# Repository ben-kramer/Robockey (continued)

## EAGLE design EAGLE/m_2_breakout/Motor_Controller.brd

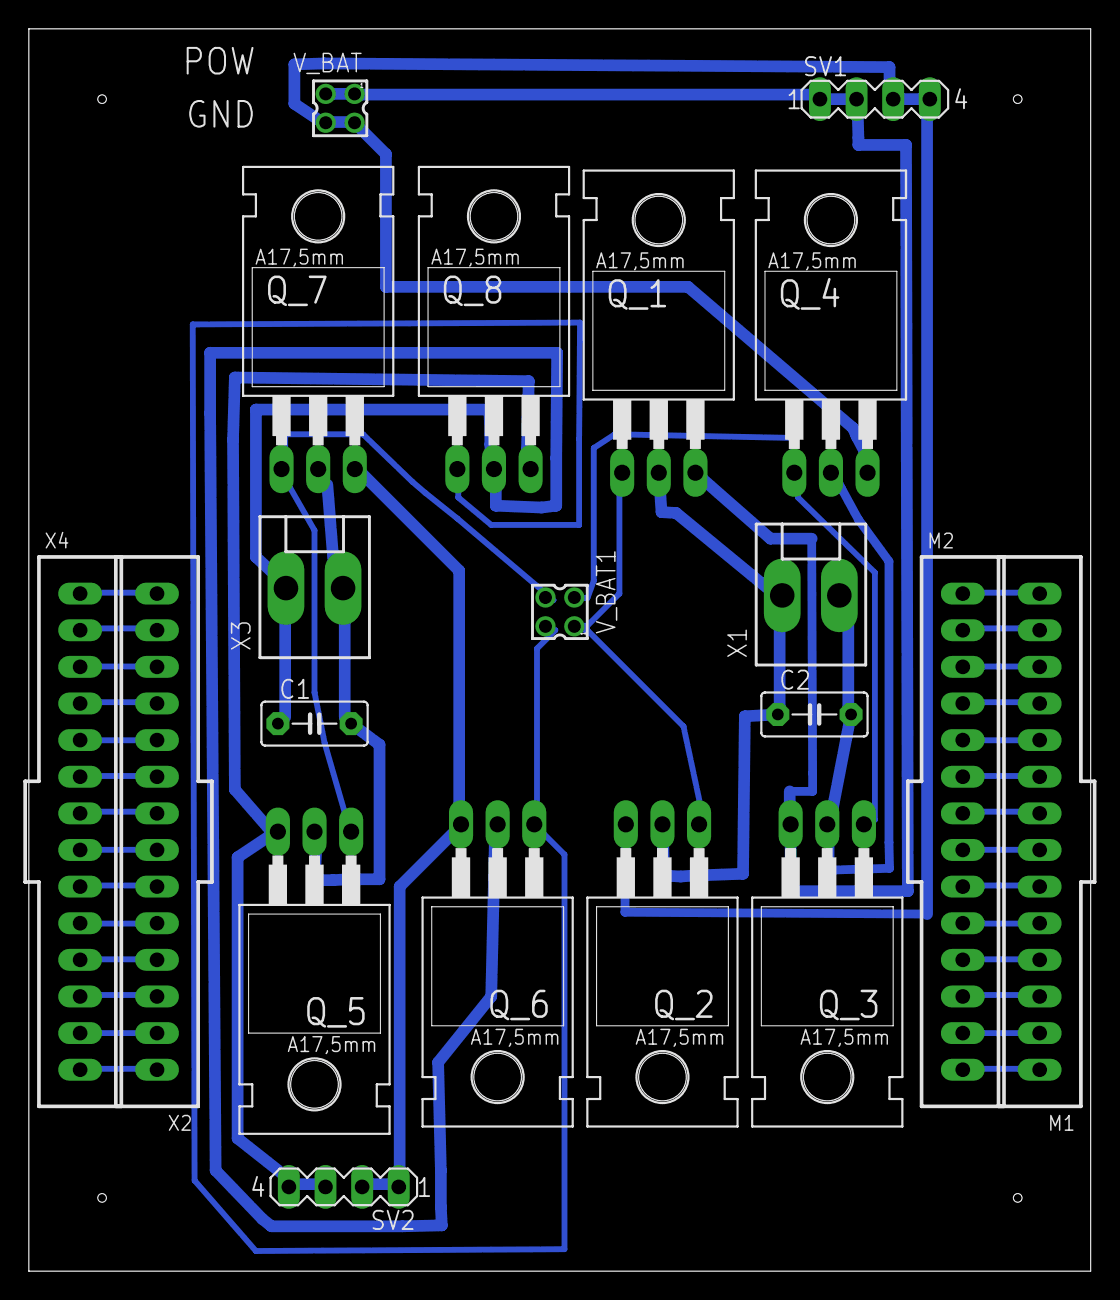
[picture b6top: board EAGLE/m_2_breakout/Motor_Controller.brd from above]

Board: 2 copper layers, 73.6 x 86.2 mm, 20 parts (0 on the bottom side), 40 nets.

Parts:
C1, C2: C5B3
M1, M2: C-GRID-14-70543; 70543-14
Q_1, Q_3, Q_6, Q_7: IRF4905; TO220BH
Q_2, Q_4, Q_5, Q_8: IRFZ48Z; TO220BH
SV1, SV2: MA04-1
V_BAT, V_BAT1: 87758-0416
X1, X3: KK-156-2
X2, X4: C-GRID-14-70543; 70543-14

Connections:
GND1: Q_2.S, Q_4.S, SV1.3, SV1.4, V_BAT.2, V_BAT.4
GND2: Q_5.S, Q_8.S, SV2.3, SV2.4
ML+: C1.1, Q_6.D, Q_8.D, X3.1
ML-: C1.2, Q_5.D, Q_7.D, X3.2
ML_G+: Q_6.G, Q_8.G, V_BAT1.2
ML_G-: Q_5.G, Q_7.G, V_BAT1.4
MR+: C2.1, Q_1.D, Q_2.D, X1.1
MR-: C2.2, Q_3.D, Q_4.D, X1.2
MR_G+: Q_1.G, Q_2.G, V_BAT1.1
MR_G-: Q_3.G, Q_4.G, V_BAT1.3
unnamed: M1.1, M2.14
unnamed: M1.2, M2.13
unnamed: M1.3, M2.12
unnamed: M1.4, M2.11
unnamed: M1.5, M2.10
unnamed: M1.6, M2.9
unnamed: M1.7, M2.8
unnamed: M1.8, M2.7
unnamed: M1.9, M2.6
unnamed: M1.10, M2.5
unnamed: M1.11, M2.4
unnamed: M1.12, M2.3
unnamed: M1.13, M2.2
unnamed: M1.14, M2.1
unnamed: X2.1, X4.14
unnamed: X2.2, X4.13
unnamed: X2.3, X4.12
unnamed: X2.4, X4.11
unnamed: X2.5, X4.10
unnamed: X2.6, X4.9
unnamed: X2.7, X4.8
unnamed: X2.8, X4.7
unnamed: X2.9, X4.6
unnamed: X2.10, X4.5
unnamed: X2.11, X4.4
unnamed: X2.12, X4.3
unnamed: X2.13, X4.2
unnamed: X2.14, X4.1
POW1: Q_1.S, Q_3.S, SV1.1, SV1.2, V_BAT.1, V_BAT.3
POW2: Q_6.S, Q_7.S, SV2.1, SV2.2

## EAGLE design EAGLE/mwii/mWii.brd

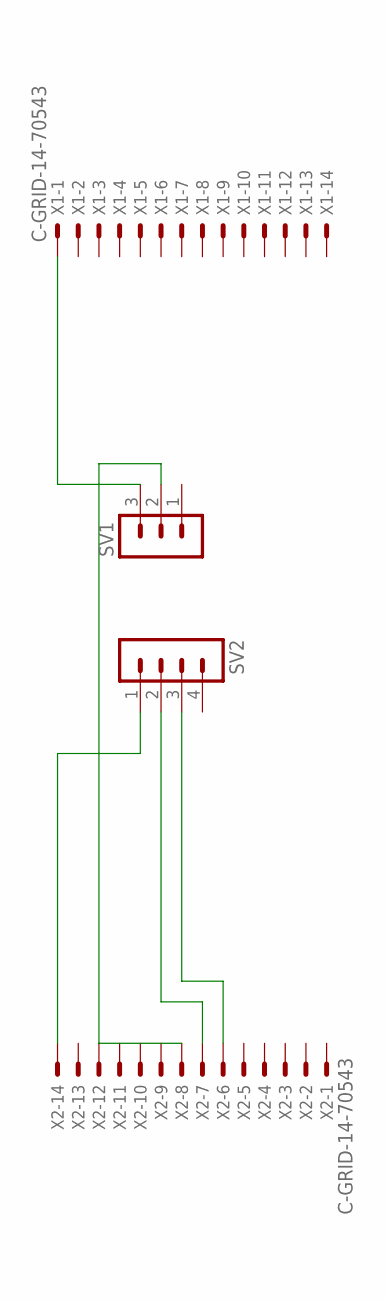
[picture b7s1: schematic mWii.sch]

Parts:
SV1: MA03-1
SV2: MA04-1
X1, X2: C-GRID-14-70543; 70543-14

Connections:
unnamed: SV2.1, X2.14
unnamed: SV1.3, X1.1
unnamed: SV1.2, X2.8
unnamed: SV2.2, X2.7
unnamed: SV2.3, X2.6

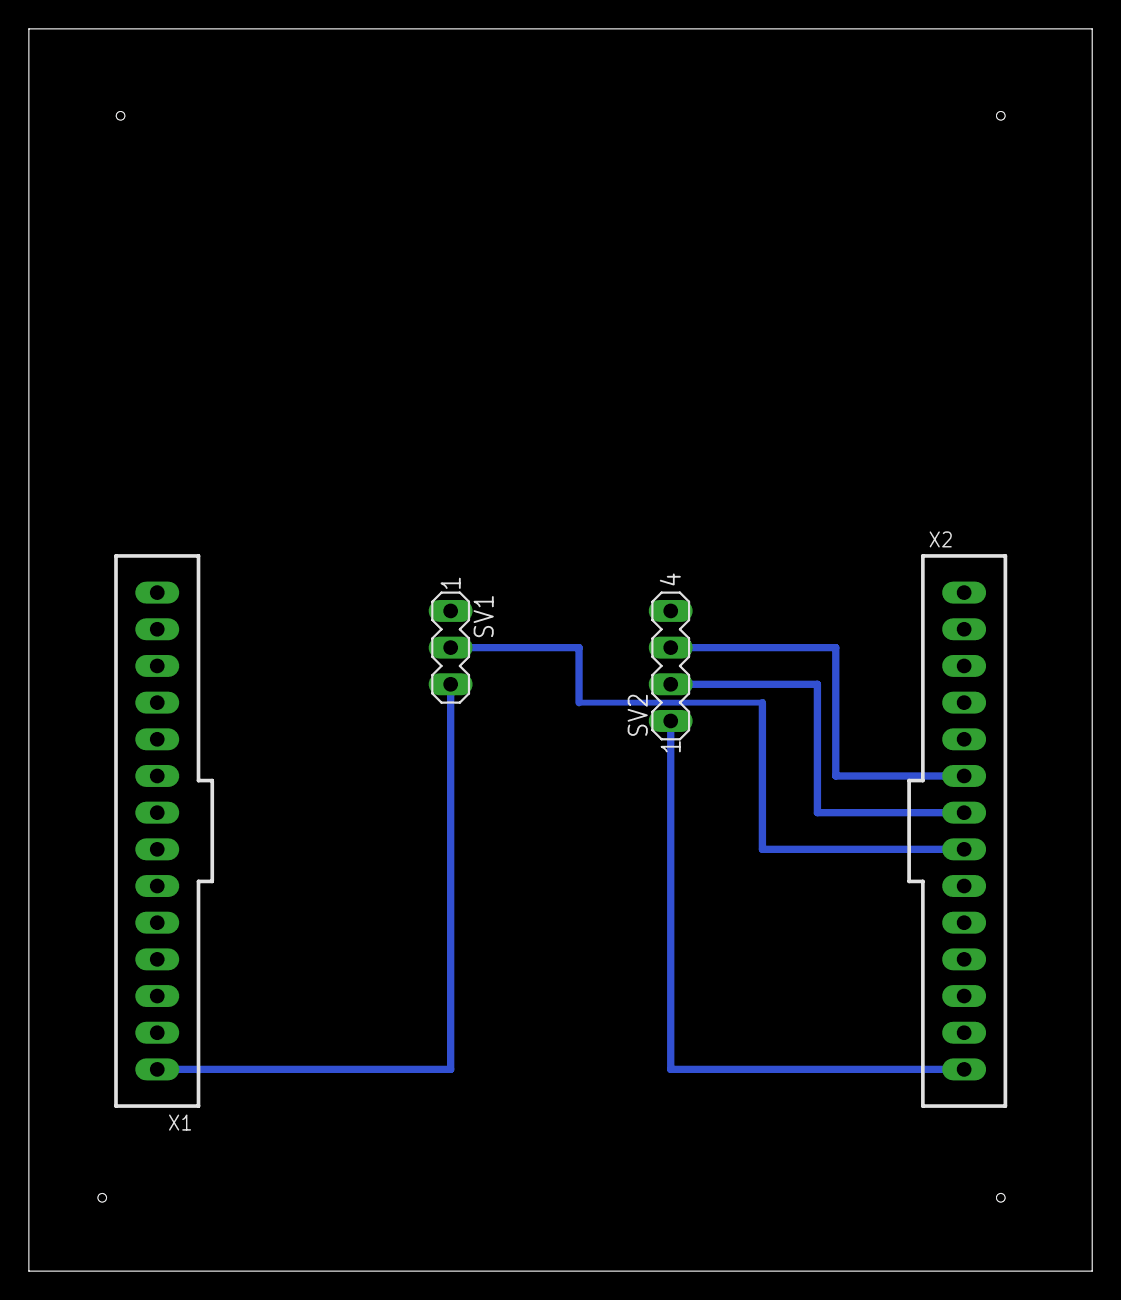
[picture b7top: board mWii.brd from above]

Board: 2 copper layers, 73.6 x 86.0 mm, 4 parts (0 on the bottom side), 5 nets.

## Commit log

2016-11-23 First robockey commit
2016-11-23 Added code and most up-to-date EAGLE files
2016-11-23 Added Solidworks
2016-11-28 First ADC code and puck finding
    ADC seems to work, I'm going to test the puck direction function next
2016-11-28 Puck finding
2016-11-29 New CAD and fixed puck finding
2016-12-01 Localize and qualifying code
2016-12-01 Added updated eagle files in folder m2_breakout
2016-12-01 Comments
2016-12-01 Fix localize code
2016-12-01 motorcode
2016-12-02 More localization
2016-12-02 Fixed compilation issues
2016-12-03 Localize complete (hopefully)
2016-12-04 Small updates
2016-12-04 brds
2016-12-05 Updated IR board: thicker traces, correct potentiometer, more extended pads for arduino shield headers.
2016-12-05 Added updated IR board schematic with correct pots
2016-12-06 Added H Bridge driving code
2016-12-06 Added m2_breakout_v2
2016-12-06 Final Cad and puck-finding edits
2016-12-07 Fixed everything about m2 board, just need optional switch rack
2016-12-07 Integrated motor PWM
2016-12-07 Fixed headers out
2016-12-07 Added m2
2016-12-07 Added switch for rink side
2016-12-07 Added new backup files
2016-12-07 M2 edits and gitignore
2016-12-07 removed backups
2016-12-07 board pdfs
2016-12-07 removed temp files
2016-12-07 Strategy functionality
    Also comm test response, determine which color we are, whether puck
    readings are valid
2016-12-09 Fixed localization, more strategy
2016-12-09 More strategy
2016-12-09 Final push
